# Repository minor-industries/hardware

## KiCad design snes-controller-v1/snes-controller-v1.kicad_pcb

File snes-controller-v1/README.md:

Using SNES controller symbol and footprint from: https://github.com/pdaehne/SNES-Userport-Adapter

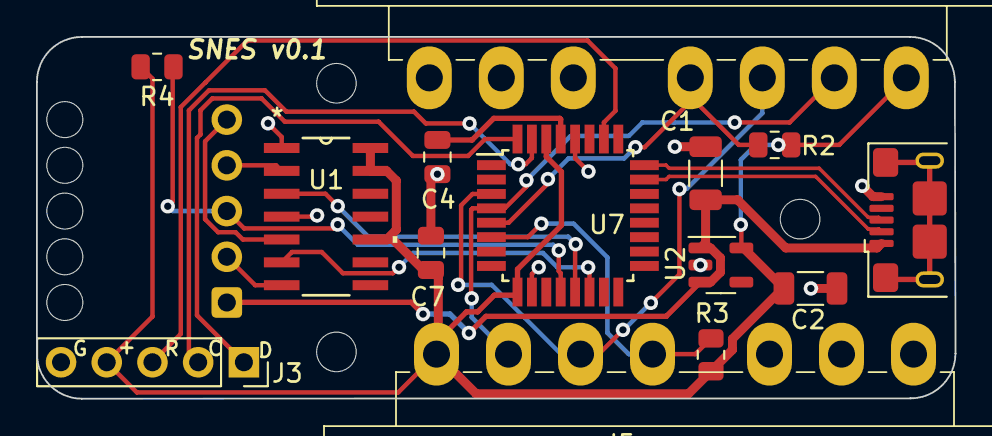
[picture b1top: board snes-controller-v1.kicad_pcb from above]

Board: 2 copper layers, 51.0 x 20.1 mm, 18 parts (1 on the bottom side), 18 nets.

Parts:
C1, C2: 10uF; C_1206_3216Metric
C4, C7: 1uF; C_0805_2012Metric
H1, H2, H3: MountingHole; MountingHole_2.2mm_M2
J1: USB_B_Micro; USB_Micro-B_Amphenol_10118193-0001LF_Horizontal
J2: NES; SolderWire-0.15sqmm_1x05_P4mm_D0.5mm_OD1.5mm_Relief
J3: Conn_01x05; PinSocket_1x05_P2.54mm_Vertical
J4, J5: SNES_Controller_Socket
R2, R3, R4: 10k; R_0805_2012Metric
U1: SN74LVC125ADR
U2: AP2112K-3.3; SOT-23-5
U7: ATSAMD21E18A-A; TQFP-32_7x7mm_P0.8mm

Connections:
+3V3: C2.1, C7.1, J3.4, J4.1 (VCC), J5.1 (VCC), R2.1, R3.1, R4.1, U1.10 (*3OE), U1.13 (*4OE), U1.14 (VCC), U2.5 (VOUT), U7.9 (VDDANA), U7.30 (VDDIN)
+5V: C1.1, J1.1 (VBUS), J2.1, U2.1 (VIN), U2.3 (EN)
/D+: J1.3 (D+), U7.24 (PA25)
/D-: J1.2 (D-), U7.23 (PA24)
/NES_CLOCK_3V: U1.6 (2Y), U7.14 (PA11)
/NES_CLOCK_5V: J2.5, U1.5 (2A)
/NES_DATA: J2.3, R4.2, U7.12 (PA09)
/NES_LATCH_3V: U1.3 (1Y), U7.13 (PA10)
/NES_LATCH_5V: J2.4, U1.2 (1A)
/PAD_CLOCK: J4.2 (Clock), J5.2 (Clock), U7.4 (PA03)
/PAD_DATA_1: J4.4 (Data), R2.2, U7.5 (PA04)
/PAD_DATA_2: J5.4 (Data), R3.2, U7.6 (PA05)
/PAD_LATCH: J4.3 (Latch), J5.3 (Latch), U7.3 (PA02)
/RESET: J3.3, U7.26 (~RESET)
/SWCLK: J3.2, U7.31 (PA30)
/SWDIO: J3.1, U7.32 (PA31)
GND: C1.2, C2.2, C4.2, C7.2, J1.5 (GND), J2.2, J3.5, J4.7 (GND), J5.7 (GND), U1.1 (*1OE), U1.4 (*2OE), U1.7 (GND), U2.2 (GND), U7.10 (GND), U7.28 (GND)
unnamed: C4.1, U7.29 (VDDCORE)

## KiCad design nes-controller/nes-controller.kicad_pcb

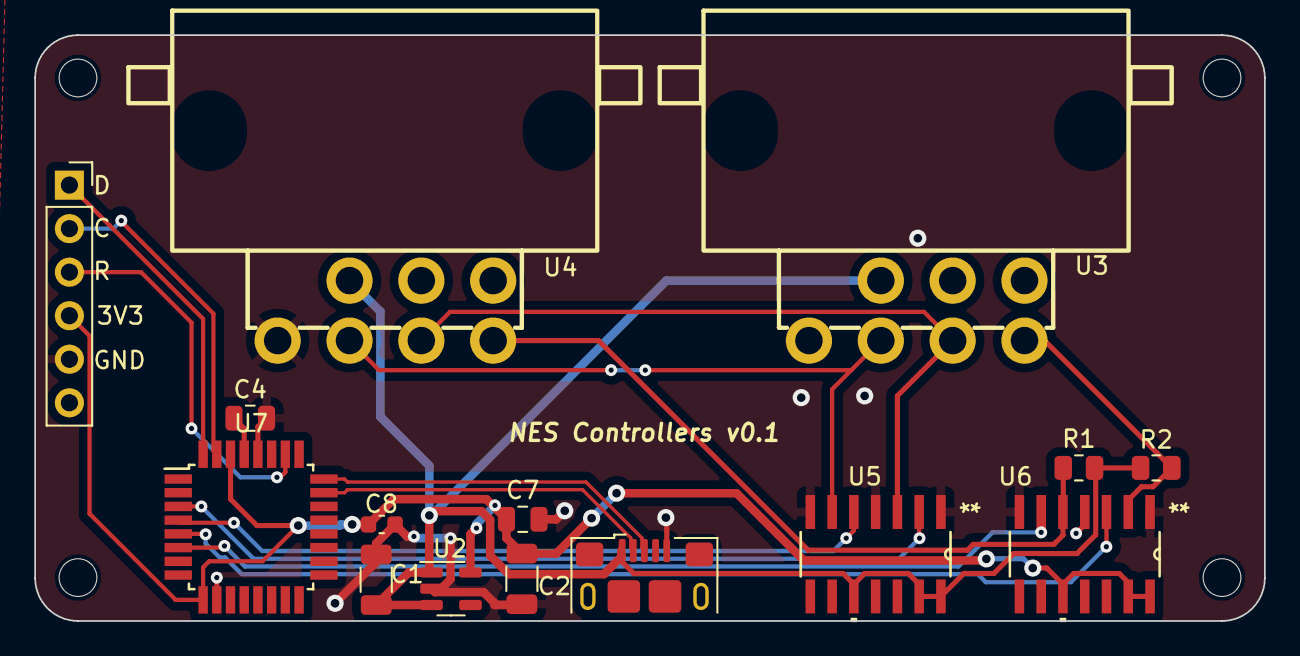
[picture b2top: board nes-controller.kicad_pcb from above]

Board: 2 copper layers, 71.8 x 34.2 mm, 19 parts (0 on the bottom side), 17 nets.

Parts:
C1, C2: 10uF; C_1206_3216Metric
C4, C7: 1uF; C_0805_2012Metric
C8: 1uF; C_0603_1608Metric
H1, H2, H3, H4: MountingHole; MountingHole_2.2mm_M2
J1: USB_B_Micro; USB_Micro-B_Amphenol_10118193-0001LF_Horizontal
J3: Conn_01x06; PinSocket_1x06_P2.54mm_Vertical
R1, R2: 10k; R_0805_2012Metric
U2: AP2112K-3.3; SOT-23-5
U3, U4: NES controller port
U5: SN74AHCT125DR
U6: SN74LVC125ADR
U7: ATSAMD21E18A-A; TQFP-32_7x7mm_P0.8mm

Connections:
+3V3: C2.1, C7.1, C8.1, J3.4, U2.5 (VOUT), U6.10 (*3OE), U6.13 (*4OE), U6.14 (VCC), U7.9 (VDDANA), U7.30 (VDDIN)
/C_3V: U5.5 (2A), U7.4 (PA03)
/C_5V: U3.5 (C), U4.5 (C), U5.6 (2Y)
/D1_3V: U6.3 (1Y), U7.5 (PA04)
/D1_5V: R2.2, U3.3 (D), U6.2 (1A)
/D2_3V: U6.6 (2Y), U7.6 (PA05)
/D2_5V: R1.2, U4.3 (D), U6.5 (2A)
/D+: J1.3 (D+), U7.24 (PA25)
/D-: J1.2 (D-), U7.23 (PA24)
/L_3V: U5.2 (1A), U7.3 (PA02)
/L_5V: U3.4 (L), U4.4 (L), U5.3 (1Y)
/RESET: J3.3, U7.26 (~RESET)
/SWCLK: J3.2, U7.31 (PA30)
/SWDIO: J3.1, U7.32 (PA31)
GND: C1.2, C2.2, C4.2, C7.2, C8.2, J1.5 (GND), J3.5, U2.2 (GND), U3.2 (G), U4.2 (G), U5.1 (*1OE), U5.4 (*2OE), U5.7 (GND), U6.1 (*1OE), U6.4 (*2OE), U6.7 (GND), U7.10 (GND), U7.28 (GND)
unnamed: C4.1, U7.29 (VDDCORE)
VBUS: C1.1, J1.1 (VBUS), R1.1, R2.1, U2.1 (VIN), U2.3 (EN), U3.1 (5V), U4.1 (5V), U5.10 (*3OE), U5.13 (*4OE), U5.14 (VCC)

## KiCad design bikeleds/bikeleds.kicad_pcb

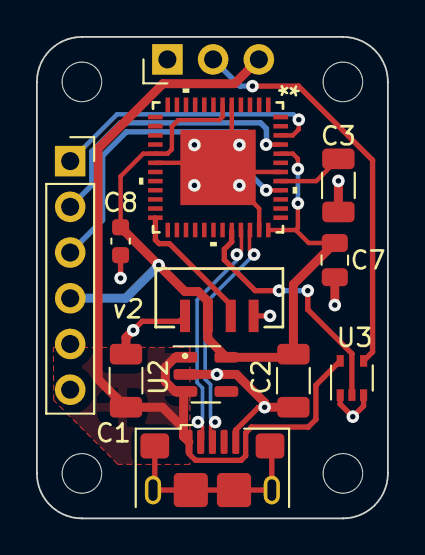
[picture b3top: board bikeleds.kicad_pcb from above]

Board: 2 copper layers, 19.5 x 26.8 mm, 16 parts (0 on the bottom side), 12 nets.

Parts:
C1, C2, C3: 10uF; C_1206_3216Metric
C7: 1uF; C_0805_2012Metric
C8: 1uF; C_0603_1608Metric
H1, H2, H3, H4: MountingHole; MountingHole_2.2mm_M2
J1: USB_B_Micro; USB_Micro-B_Amphenol_10118193-0001LF_Horizontal
J2: Conn_01x03_Pin; PinHeader_1x03_P2.54mm_Vertical
J3: Conn_01x06; PinSocket_1x06_P2.54mm_Vertical
U1: ATSAMD51G19A-MU; QFN48_7X7MC_MCH
U2: AP2112K-3.3; SOT-23-5
U3: 74AHCT1G125; SOT-353_SC-70-5
U4: TSOP77438TT; IC4_TSOP77438TT_VIS-M

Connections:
+3V3: C2.1, C7.1, C8.1, J3.4, U1.6 (VDDANA), U1.17 (VDDIO), U1.36 (VDDIO), U1.44 (VDDIO), U2.5 (VOUT), U4.2 (VS)
/D+: J1.3 (D+), U1.34 (PA25)
/D-: J1.2 (D-), U1.33 (PA24)
/IR: U1.24 (PA15), U4.3 (OUT)
/LEDS_IN: U1.32 (PA23), U3.2
/LEDS_OUT: J2.2, U3.4
/RESET: J3.3, U1.40 (RESETN)
/SWCLK: J3.2, U1.45 (PA30)
/SWDIO: J3.1, U1.46 (PA31)
GND: C1.2, C2.2, C3.2, C7.2, C8.2, J1.5 (GND), J2.1, J3.5, U1.5 (GND), U1.18 (GND), U1.35 (GND), U1.42 (GND), U1.49 (EPAD), U2.2 (GND), U3.1, U3.3 (GND), U4.1 (GND), U4.4 (GND)
unnamed: C3.1, U1.41 (VDDCORE)
VBUS: C1.1, J1.1 (VBUS), J2.3, U2.1 (VIN), U2.3 (EN), U3.5 (VCC)

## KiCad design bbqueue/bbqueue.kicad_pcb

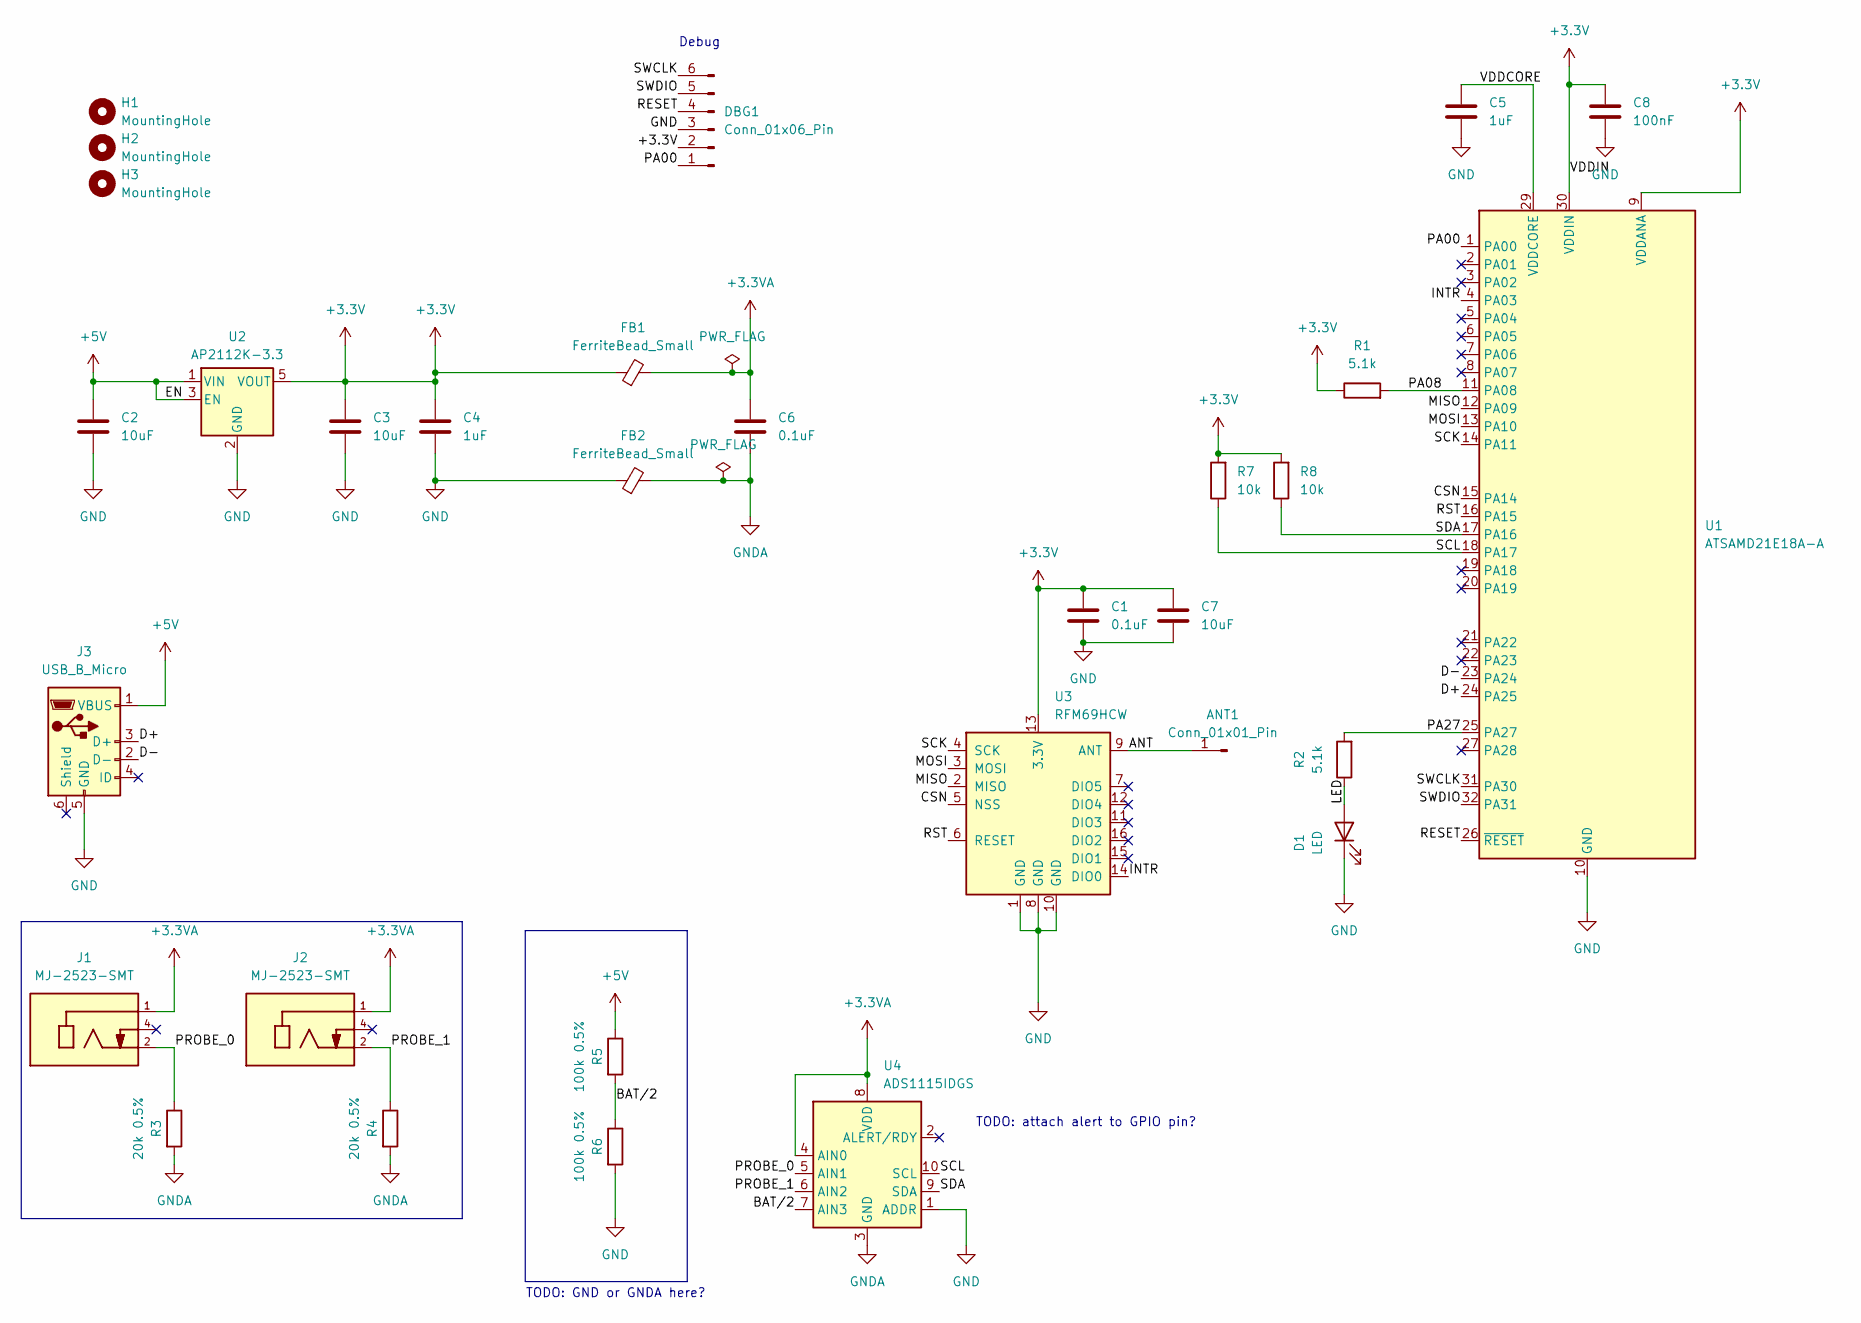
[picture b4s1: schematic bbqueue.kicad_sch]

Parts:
ANT1: Conn_01x01_Pin; Pin_D1.0mm_L10.0mm
C1, C6: 0.1uF; C_0805_2012Metric
C2, C3: 10uF; C_0805_2012Metric
C4, C5: 1uF; C_0805_2012Metric
C7: 10uF; C_1206_3216Metric
C8: 100nF; C_0805_2012Metric
D1: LED; LED_0805_2012Metric
DBG1: Conn_01x06_Pin; PinHeader_1x06_P2.54mm_Vertical
FB1, FB2: FerriteBead_Small; L_0805_2012Metric
H1, H2, H3: MountingHole; MountingHole_2.2mm_M2
J1, J2: MJ-2523-SMT; CUI_MJ-2523-SMT; PART_REV 1.02
J3: USB_B_Micro; USB_Micro-B_Amphenol_10118193-0001LF_Horizontal
R1, R2: 5.1k; R_0805_2012Metric
R3, R4: 20k 0.5%; R_1206_3216Metric
R5, R6: 100k 0.5%; R_0805_2012Metric
R7, R8: 10k; R_0805_2012Metric
U1: ATSAMD21E18A-A; TQFP-32_7x7mm_P0.8mm
U2: AP2112K-3.3; SOT-23-5
U3: RFM69HCW; HOPERF_RFM9XW_SMD
U4: ADS1115IDGS; TSSOP-10_3x3mm_P0.5mm

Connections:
+3.3V: C1.1, C3.1, C4.1, C7.1, C8.1, DBG1.2, FB1.1, R1.1, R7.2, R8.2, U1.9 (VDDANA), U1.30 (VDDIN), U2.5 (VOUT), U3.13 (3.3V)
+3.3VA: C6.1, FB1.2, J1.1, J2.1, U4.4 (AIN0), U4.8 (VDD)
+5V: C2.1, J3.1 (VBUS), R5.1, U2.1 (VIN), U2.3 (EN)
/ANT: ANT1.1, U3.9 (ANT)
/BAT/2: R5.2, R6.1, U4.7 (AIN3)
/CSN: U1.15 (PA14), U3.5 (NSS)
/D+: J3.3 (D+), U1.24 (PA25)
/D-: J3.2 (D-), U1.23 (PA24)
/INTR: U1.4 (PA03), U3.14 (DIO0)
/LED: D1.2 (A), R2.1
/MISO: U1.12 (PA09), U3.2 (MISO)
/MOSI: U1.13 (PA10), U3.3 (MOSI)
/PA00: DBG1.1, U1.1 (PA00)
/PA08: R1.2, U1.11 (PA08)
/PA27: R2.2, U1.25 (PA27)
/PROBE_0: J1.2, R3.1, U4.5 (AIN1)
/PROBE_1: J2.2, R4.1, U4.6 (AIN2)
/RESET: DBG1.4, U1.26 (~RESET)
/RST: U1.16 (PA15), U3.6 (RESET)
/SCK: U1.14 (PA11), U3.4 (SCK)
/SCL: R7.1, U1.18 (PA17), U4.10 (SCL)
/SDA: R8.1, U1.17 (PA16), U4.9 (SDA)
/SWCLK: DBG1.6, U1.31 (PA30)
/SWDIO: DBG1.5, U1.32 (PA31)
/VDDCORE: C5.1, U1.29 (VDDCORE)
GND: C1.2, C2.2, C3.2, C4.2, C5.2, C7.2, C8.2, D1.1 (K), DBG1.3, FB2.1, J3.5 (GND), R6.2, U1.10 (GND), U1.28 (GND), U2.2 (GND), U3.1 (GND), U3.8 (GND), U3.10 (GND), U4.1 (ADDR)
GNDA: C6.2, FB2.2, R3.2, R4.2, U4.3 (GND)

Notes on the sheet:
Debug
TODO: GND or GNDA here?
TODO: attach alert to GPIO pin?

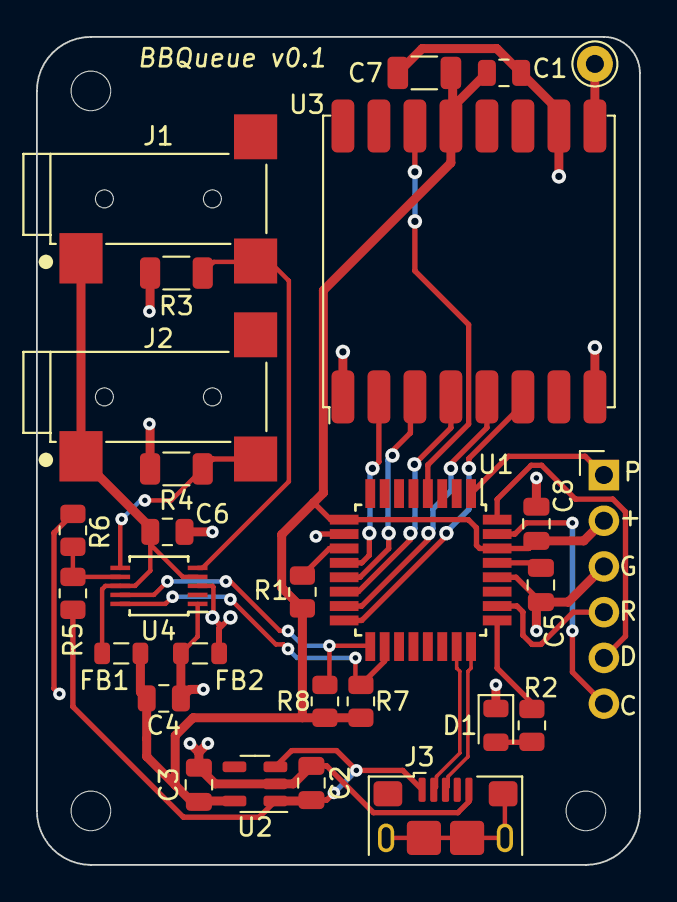
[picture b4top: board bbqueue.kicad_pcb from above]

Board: 2 copper layers, 33.5 x 46.0 mm, 31 parts (0 on the bottom side), 27 nets.

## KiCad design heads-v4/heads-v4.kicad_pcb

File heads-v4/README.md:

# The Heads raspberry pi expansion board

This is an [Adafruit Seesaw](https://www.adafruit.com/product/3657)-based raspberry pi HAT that provides:

- Constant current LED driver for IR (based on TPS92201)
- Stepper motor driver (based on DRV8833)
- ws2812 led control with level shifting
- i2c pass through for magnet sensor (stemma connector)
- SWD programming interface

The code can be found here: [github.com/minor-industries/theheads](https://github.com/minor-industries/theheads)

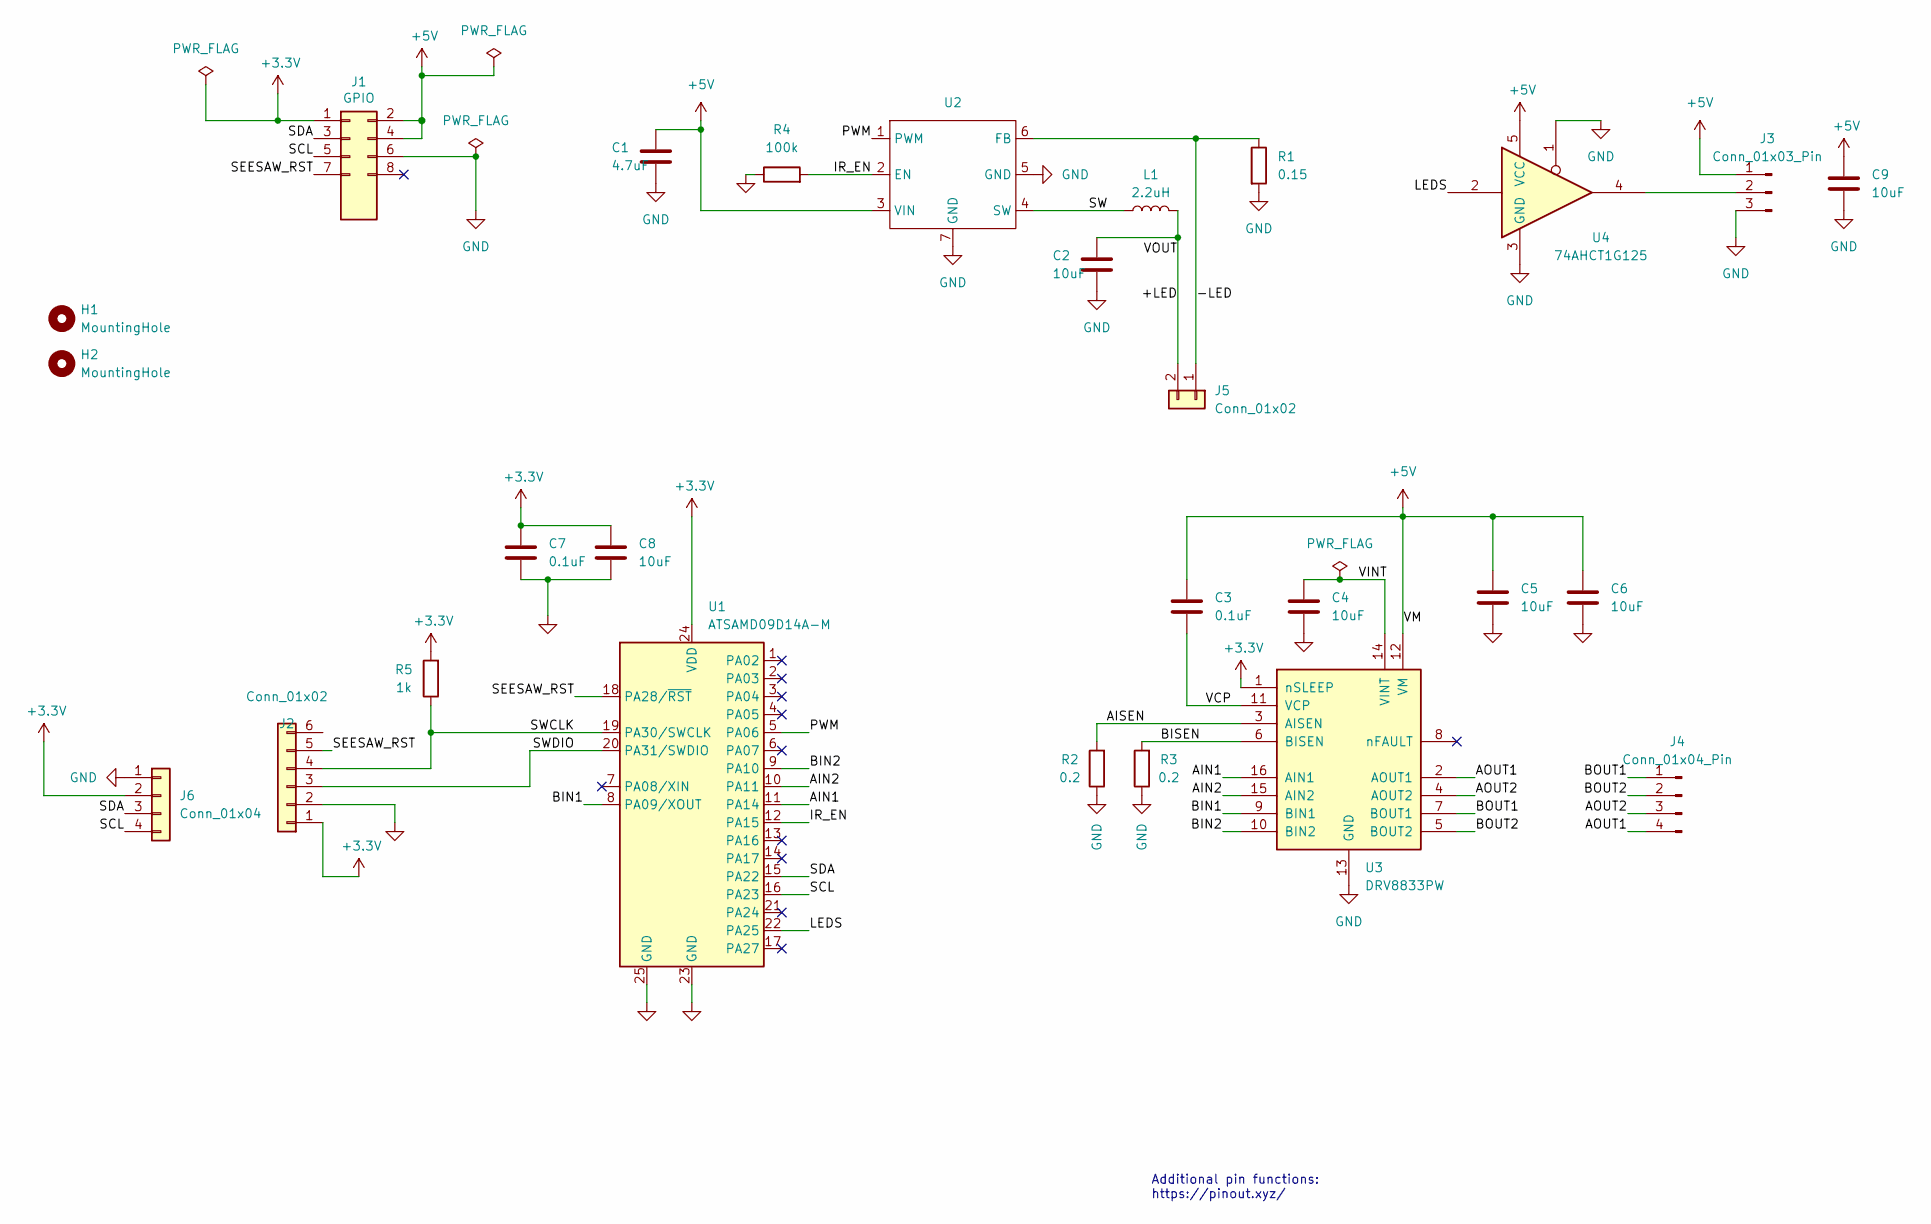
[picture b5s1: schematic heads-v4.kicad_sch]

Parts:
C1: 4.7uF; C_0805_2012Metric
C2: 10uF; C_0805_2012Metric
C3, C7: 0.1uF; C_0805_2012Metric
C4, C5, C6, C8, C9: 10uF; C_1206_3216Metric
H1, H2: MountingHole; MountingHole_2.7mm_M2.5
J1: GPIO; PinSocket_2x06_P2.54mm_Vertical
J2: Conn_01x02; PinHeader_1x06_P2.54mm_Vertical
J3: Conn_01x03_Pin; PinHeader_1x03_P2.54mm_Vertical_SMD_Pin1Left
J4: Conn_01x04_Pin; PinHeader_1x04_P2.54mm_Vertical_SMD_Pin1Left
J5: Conn_01x02; TerminalBlock_4Ucon_1x02_P3.50mm_Horizontal
J6: Conn_01x04; JST_SH_BM04B-SRSS-TB_1x04-1MP_P1.00mm_Vertical
L1: 2.2uH; Induct_1
R1: 0.15; R_0805_2012Metric
R2, R3: 0.2; R_0805_2012Metric
R4: 100k; R_0805_2012Metric
R5: 1k; R_0805_2012Metric
U1: ATSAMD09D14A-M; QFN-24-1EP_4x4mm_P0.5mm_EP2.6x2.6mm
U2: WSON-6-1EP_2x2mm_P0.65mm_EP1x1.6mm_ThermalVias
U3: DRV8833PW; TSSOP-16_4.4x5mm_P0.65mm
U4: 74AHCT1G125; SOT-353_SC-70-5

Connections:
+3V3: C7.1, C8.1, J1.1, J2.1, J6.2, R5.2, U1.24 (VDD), U3.1 (nSLEEP)
+5V: C1.2, C3.1, C5.1, C6.1, C9.1, J1.2, J1.4, J3.1, U2.3 (VIN), U3.12 (VM), U4.5 (VCC)
/+LED: C2.2, J5.2, L1.2
/-LED: J5.1, R1.1, U2.6 (FB)
/AIN1: U1.11 (PA14), U3.16 (AIN1)
/AIN2: U1.10 (PA11), U3.15 (AIN2)
/AISEN: R2.2, U3.3 (AISEN)
/AOUT1: J4.4, U3.2 (AOUT1)
/AOUT2: J4.3, U3.4 (AOUT2)
/BIN1: U1.8 (PA09/XOUT), U3.9 (BIN1)
/BIN2: U1.9 (PA10), U3.10 (BIN2)
/BISEN: R3.2, U3.6 (BISEN)
/BOUT1: J4.1, U3.7 (BOUT1)
/BOUT2: J4.2, U3.5 (BOUT2)
/IR_EN: R4.2, U1.12 (PA15), U2.2 (EN)
/LEDS: U1.22 (PA25), U4.2
/PWM: U1.5 (PA06), U2.1 (PWM)
/SCL: J1.5, J6.4, U1.16 (PA23)
/SDA: J1.3, J6.3, U1.15 (PA22)
/SEESAW_RST: J1.7, J2.5, U1.18 (PA28/~RST)
/SW: L1.1, U2.4 (SW)
/SWCLK: J2.4, R5.1, U1.19 (PA30/SWCLK)
/SWDIO: J2.3, U1.20 (PA31/SWDIO)
/VCP: C3.2, U3.11 (VCP)
/VINT: C4.1, U3.14 (VINT)
GND: C1.1, C2.1, C4.2, C5.2, C6.2, C7.2, C8.2, C9.2, J1.6, J2.2, J3.3, J6.1, R1.2, R2.1, R3.1, R4.1, U1.23 (GND), U1.25 (GND), U2.5 (GND), U2.7 (GND), U3.13 (GND), U4.1, U4.3 (GND)
unnamed: J3.2, U4.4

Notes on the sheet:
Additional pin functions: https://pinout.xyz/

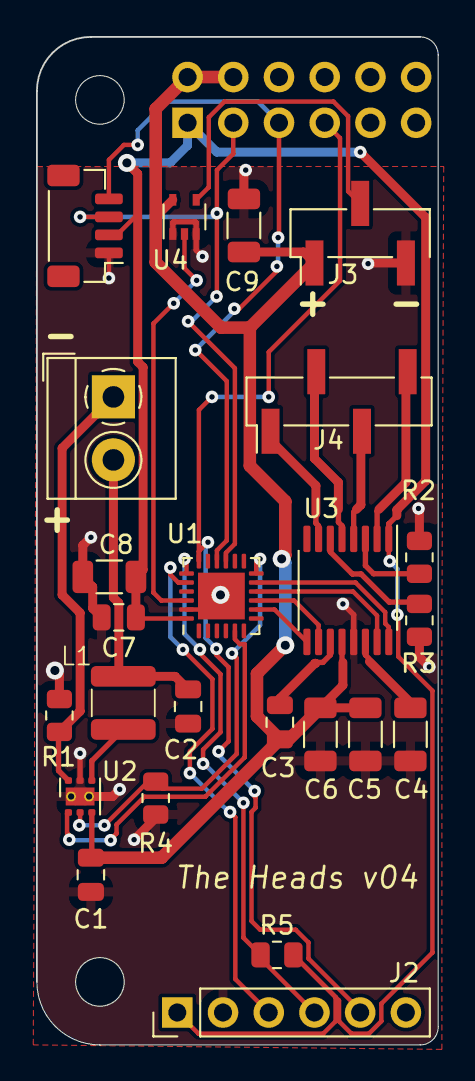
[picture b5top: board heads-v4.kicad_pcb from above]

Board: 2 copper layers, 22.3 x 56.0 mm, 27 parts (1 on the bottom side), 27 nets.

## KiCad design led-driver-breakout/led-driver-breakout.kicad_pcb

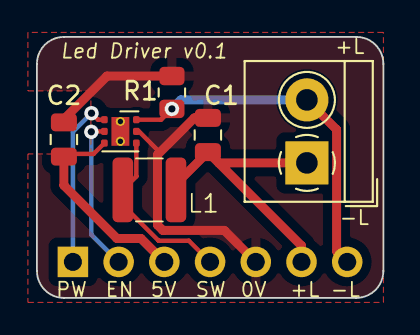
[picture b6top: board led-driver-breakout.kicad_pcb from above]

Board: 2 copper layers, 19.2 x 14.5 mm, 7 parts (0 on the bottom side), 7 nets.

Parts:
C1: 10uF; C_0805_2012Metric
C2: 4.7uF; C_0805_2012Metric
J1: Conn_01x07_Pin; PinHeader_1x07_P2.54mm_Vertical
J2: Conn_01x02_Pin; TerminalBlock_4Ucon_1x02_P3.50mm_Horizontal
L1: 2.2uH; Induct_1
R1: R; R_0805_2012Metric
U1: WSON-6-1EP_2x2mm_P0.65mm_EP1x1.6mm_ThermalVias

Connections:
+5V: C2.2, J1.3, U1.3 (VIN)
/+LED: C1.2, J1.6, J2.1, L1.2
/-LED: J1.7, J2.2, R1.1, U1.6 (FB)
/EN: J1.2, U1.2 (EN)
/PWM: J1.1, U1.1 (PWM)
/SW: J1.4, L1.1, U1.4 (SW)
GND: C1.1, C2.1, J1.5, R1.2, U1.5 (GND)

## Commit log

2024-01-27 gitignore
2024-02-28 v2 of bikeleds
2024-03-05 add start of heads-v3
2024-03-06 rename
2024-03-06 tweak
2024-04-15 move old stuff to archive
2024-04-15 Add readme for theheads
2025-04-26 ship
2025-04-26 fork v2
2025-04-26 fork v3 controller
2025-04-26 nes v2
2025-04-26 fix pour issue
2025-04-26 nes controller
2025-04-26 fork nes -> snes
2025-04-26 update controller port
2025-04-26 update socket on PCB
2025-04-26 ground plane
